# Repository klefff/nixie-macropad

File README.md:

# nixie-macropad

</p>

Simple 2x3 macropad with encoder that has a 3 digit nixie tube display that can be programmed for various functions over QMK.

## Usage:
Feel free to try replicate with care, as this is an unpolished proof of concept that I will probably build on later. Enjoy!

### Hardware Notes:
- Not sure but it seems the boards that I am using to drive the Nixie tubes [might be discontinued](https://www.tindie.com/products/dekuNukem/exixe-miniture-nixie-tube-driver-modules/). However the developer open-sourced them, so you might be able to make them yourself. (Planning to make my own for future builds)

## Main Features:
- 3x IN-14 Nixie Tubes with numbers 0-9 plus left comma
- Uses [QMK](https://qmk.fm/)
- Display current volume of connected Windows device [via RAWHID](https://github.com/BlankSourceCode/qmk-hid-display)
- EC11 Encoder + button
- 2x3 Macropad with Kailh Hotswap
- Only USB connected to PC needed

## Software Installation:
### Windows Node Script:
1. Download the 'Node Script' folder
1. Follow the steps in 'Development Setup' and/or 'Using the Script' from [BlankSourceCode's repo](https://au.element14.com/harwin/m20-7821246/connector-rcpt-12pos-2-54mm-1row/dp/3225929) 

### QMK:
1. You need to flash the Pro Micro with custom QMK firmware
    - Fork: [Use my fork](https://github.com/klefff/qmk_firmware/)
    - How to flash: [QMK Docs](https://docs.qmk.fm/#/newbs_flashing)
1. Build for [Phi (Default)](https://github.com/klefff/qmk_firmware/tree/master/keyboards/phi)

## Hardware:
### Before Assembling:
1. For the Exixes, you need to attach the Nixie tubes to the boards. 
    - I just soldered machine sockets to the boards and shoved the Nixie tube pins into the sockets (gingerly)
    - Or follow their [recommended method](https://github.com/dekuNukem/exixe/blob/master/getting_started.md)
### Assembly
1. Make the custom PCBs (needs 2, or make a case)
1. Solder on the required components below (see pictures)
1. Assemble such that two of the custom PCBs make a basic case thing
1. Choose some cool keycaps and knob

</p>
</p>
</p>
</p>

## Bill of Materials:
- 2x Custom PCBS
    - Sandwich with 7x 15mm standoffs (M3 Size)
- 3x [Exixe](https://github.com/dekuNukem/exixe)
    - Nixie tube driver modules with SPI communication
- 3x IN-14 Nixie Tubes with 0-9 digit and left comma (at least)
- 1x Pro Micro or similar pinout with QMK support
- 2x Custom base PCB that doubles as stand
    - See PCB build files
- 6x Kailh Hotswap switch sockets
- 1x [2.5-15VDC to 170VDC DC-DC convertor](https://omnixie.com/products/nch8200hv-nixie-hv-power-module) or similar
- 1x Any type of EC11 rotary encoder
    - [I used this one](https://www.digikey.com.au/en/products/detail/bourns-inc/PEC11R-4020K-S0024/4499637)
- 1x [SMD 3.3V Voltage Regulator](https://au.element14.com/stmicroelectronics/ld1117s33ctr/ic-v-reg-ldo-3-3v-smd/dp/146777902)
    - Needed to power the Exixes
- 3x 10uF [Electrolytic Capacitors](https://au.element14.com/wurth-elektronik/865230542002/cap-10-f-35v-smd/dp/2466435)
    - Required for the Voltage Reg
- 1x 0.1uF [Ceramic Capacitor](https://au.element14.com/yageo/cc0805krx7r8bb104/cap-0-1-f-25v-10-x7r-0805/dp/644249)
- 7x [Diodes](https://www.digikey.com.au/en/products/detail/onsemi/1N4148/458603)
- 3x [470 Ohm SMD Resistors](https://au.element14.com/multicomp-pro/mc0805s8f4700t5e/res-thick-film-470r-1-0-125w-0805/dp/1632491)
- Some 2.54mm pitch connectors (if you don't want to direct solder)
    - I like [machine sockets](https://www.digikey.com.au/en/products/detail/adam-tech/SMC-1-40-1-GT/9831942) but normal ['Arduino'-esque ones are good too](https://au.element14.com/harwin/m20-7821246/connector-rcpt-12pos-2-54mm-1row/dp/3225929)
    - 3x 7 pin for Exixe comms
    - 2x 12 pin for Pro Micro
    - 7x 1 pin (if you can find them or just cut bigger ones)
        - For 170V DC-DC convertor and Exixe 170V
    - 2x 2 pin for Exixe 3V
    - For the above 2, you can also just get 7 pin ones and take out the middle 4 pins
- Some keycaps
- An encoder knob

## Additional:
### Housekeeping:
- Every ~15 mins the tubes will cycle all digits to reduce change of cathode poisoning

### Future Work:
- Possible adding VIA capabilities for flashing
- Adding more uses for the 3 tube digits; current weather, CPU usage etc
- Adding another digit for RTC time
- Bluetooth/Wireless with battery

## References:
- [Exixe](https://github.com/dekuNukem/exixe)
- [RAW HID communication via node script](https://github.com/BlankSourceCode/qmk-hid-display)

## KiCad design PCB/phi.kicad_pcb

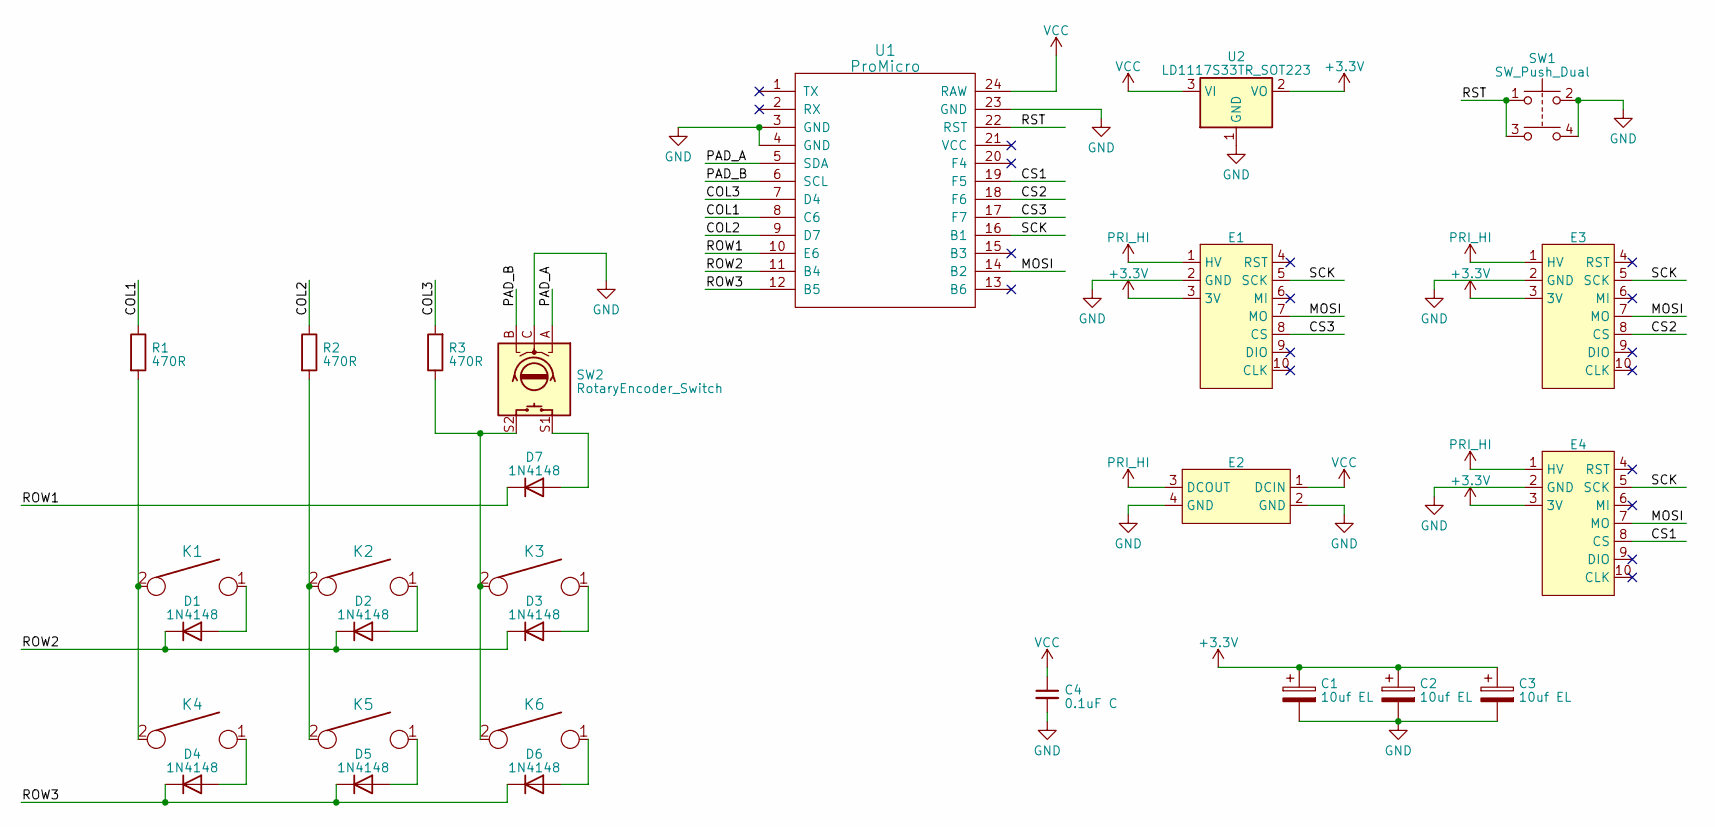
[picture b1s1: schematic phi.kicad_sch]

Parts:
C1, C2, C3: 10uf EL; CP_Elec_5x5.8
C4: 0.1uF C; C_0201_0603Metric_Pad0.64x0.40mm_HandSolder
D1, D2, D3, D4, D5, D6, D7: 1N4148; D_DO-35_SOD27_P7.62mm_Horizontal
E1, E3, E4: exixe14
E2: NCH8200HV
K1, K2, K3, K4, K5, K6: KEYSW; SW_Cherry_MX_1.00u_PCB
R1, R2, R3: 470R; R_0805_2012Metric_Pad1.20x1.40mm_HandSolder
SW1: SW_Push_Dual; TACTILE_SWITCH_SMD_5.2MM
SW2: RotaryEncoder_Switch; RotaryEncoder_Alps_EC11E-Switch_Vertical_H20mm
U1: ProMicro
U2: LD1117S33TR_SOT223; SOT-223-3_TabPin2

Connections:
+3.3V: C1.1, C2.1, C3.1, E1.3 (3V), E3.3 (3V), E4.3 (3V), U2.2 (VO)
/COL1: R1.1, U1.8 (C6)
/COL2: R2.1, U1.9 (D7)
/COL3: R3.2, U1.7 (D4)
/CS1: E4.8 (CS), U1.19 (F5)
/CS2: E3.8 (CS), U1.18 (F6)
/CS3: E1.8 (CS), U1.17 (F7)
/MOSI: E1.7 (MO), E3.7 (MO), E4.7 (MO), U1.14 (B2)
/PAD_A: SW2.A, U1.5 (SDA)
/PAD_B: SW2.B, U1.6 (SCL)
/ROW1: D7.1 (K), U1.10 (E6)
/ROW2: D1.1 (K), D2.1 (K), D3.1 (K), U1.11 (B4)
/ROW3: D4.1 (K), D5.1 (K), D6.1 (K), U1.12 (B5)
/RST: SW1.1, SW1.3, U1.22 (RST)
/SCK: E1.5 (SCK), E3.5 (SCK), E4.5 (SCK), U1.16 (B1)
GND: C1.2, C2.2, C3.2, C4.2, E1.2 (GND), E2.2 (GND), E2.4 (GND), E3.2 (GND), E4.2 (GND), SW1.2, SW1.4, SW2.C, U1.3 (GND), U1.4 (GND), U1.23 (GND), U2.1 (GND)
unnamed: D1.2 (A), K1.1
unnamed: D2.2 (A), K2.1
unnamed: D3.2 (A), K3.1
unnamed: D4.2 (A), K4.1
unnamed: D5.2 (A), K5.1
unnamed: D6.2 (A), K6.1
unnamed: D7.2 (A), SW2.S1
unnamed: K1.2, K4.2, R1.2
unnamed: K2.2, K5.2, R2.2
unnamed: K3.2, K6.2, R3.1, SW2.S2
PRI_HI: E1.1 (HV), E2.3 (DCOUT), E3.1 (HV), E4.1 (HV)
VCC: C4.1, E2.1 (DCIN), U1.24 (RAW), U2.3 (VI)

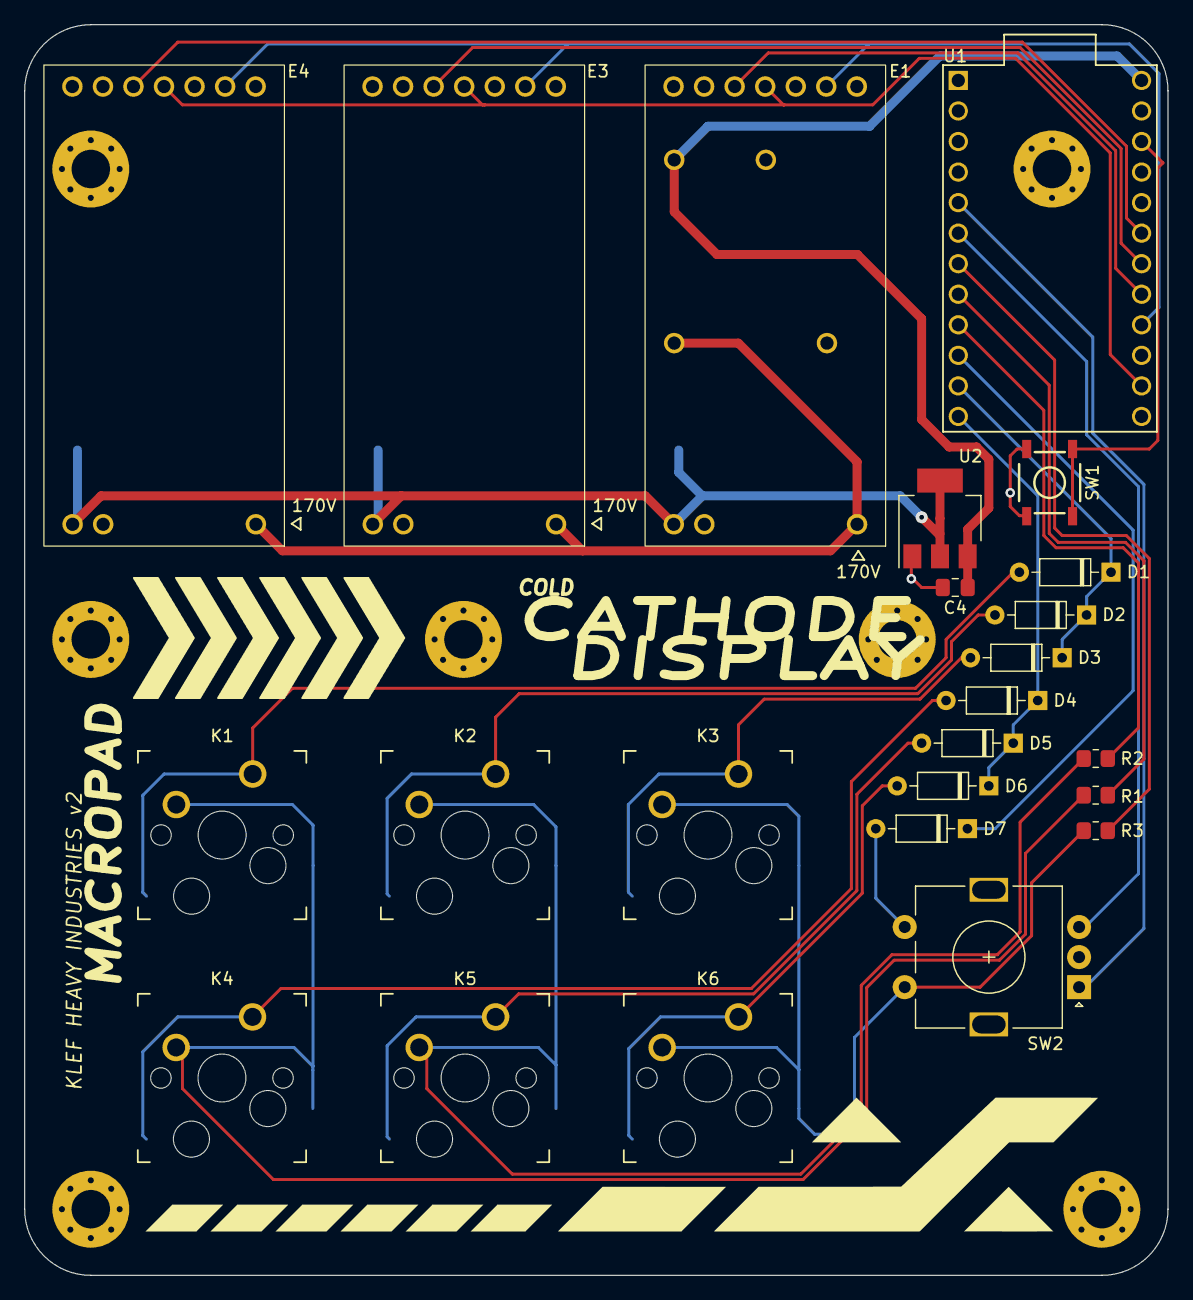
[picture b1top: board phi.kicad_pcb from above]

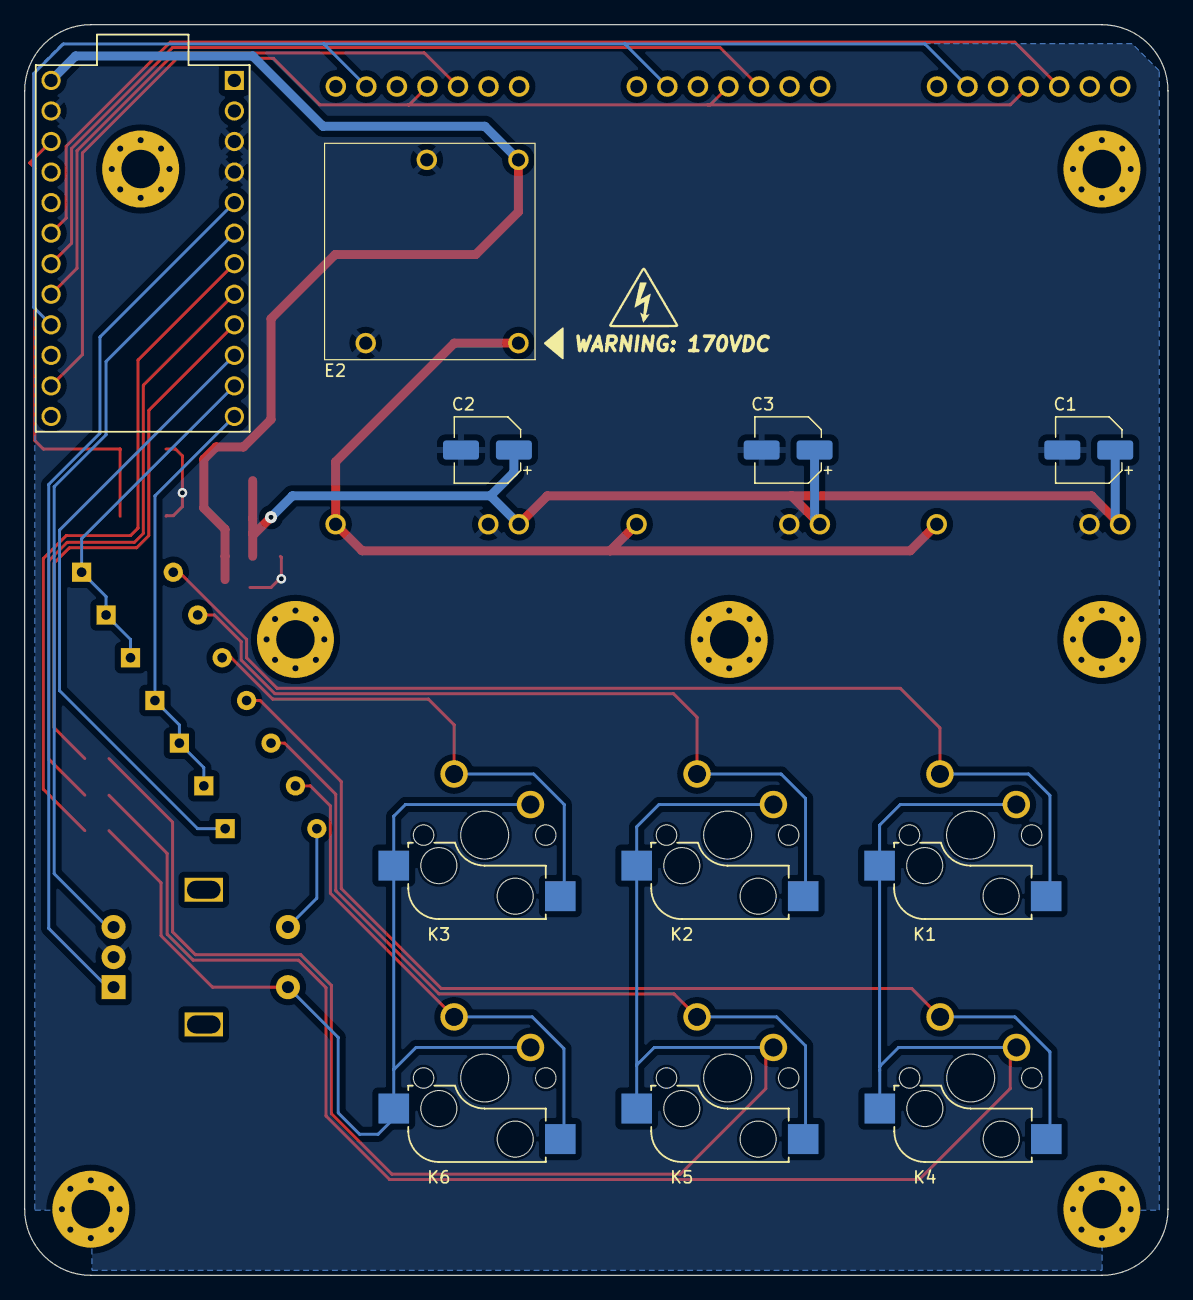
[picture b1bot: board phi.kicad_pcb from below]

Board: 2 copper layers, 95.1 x 104.0 mm, 28 parts (4 on the bottom side), 28 nets.

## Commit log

2023-04-24 added pcb files
2023-04-24 added node script
2023-04-25 added tube protection
2023-04-26 moved tube protection to qmk
2023-04-27 completely moved tube refresh to qmk
